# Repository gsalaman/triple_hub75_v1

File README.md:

# triple_hub75_v1
 Pi to 3 RGB chain board design

PDF:
[schematic.pdf](https://github.com/gsalaman/triple_hub75_v1/files/3968266/schematic.pdf)

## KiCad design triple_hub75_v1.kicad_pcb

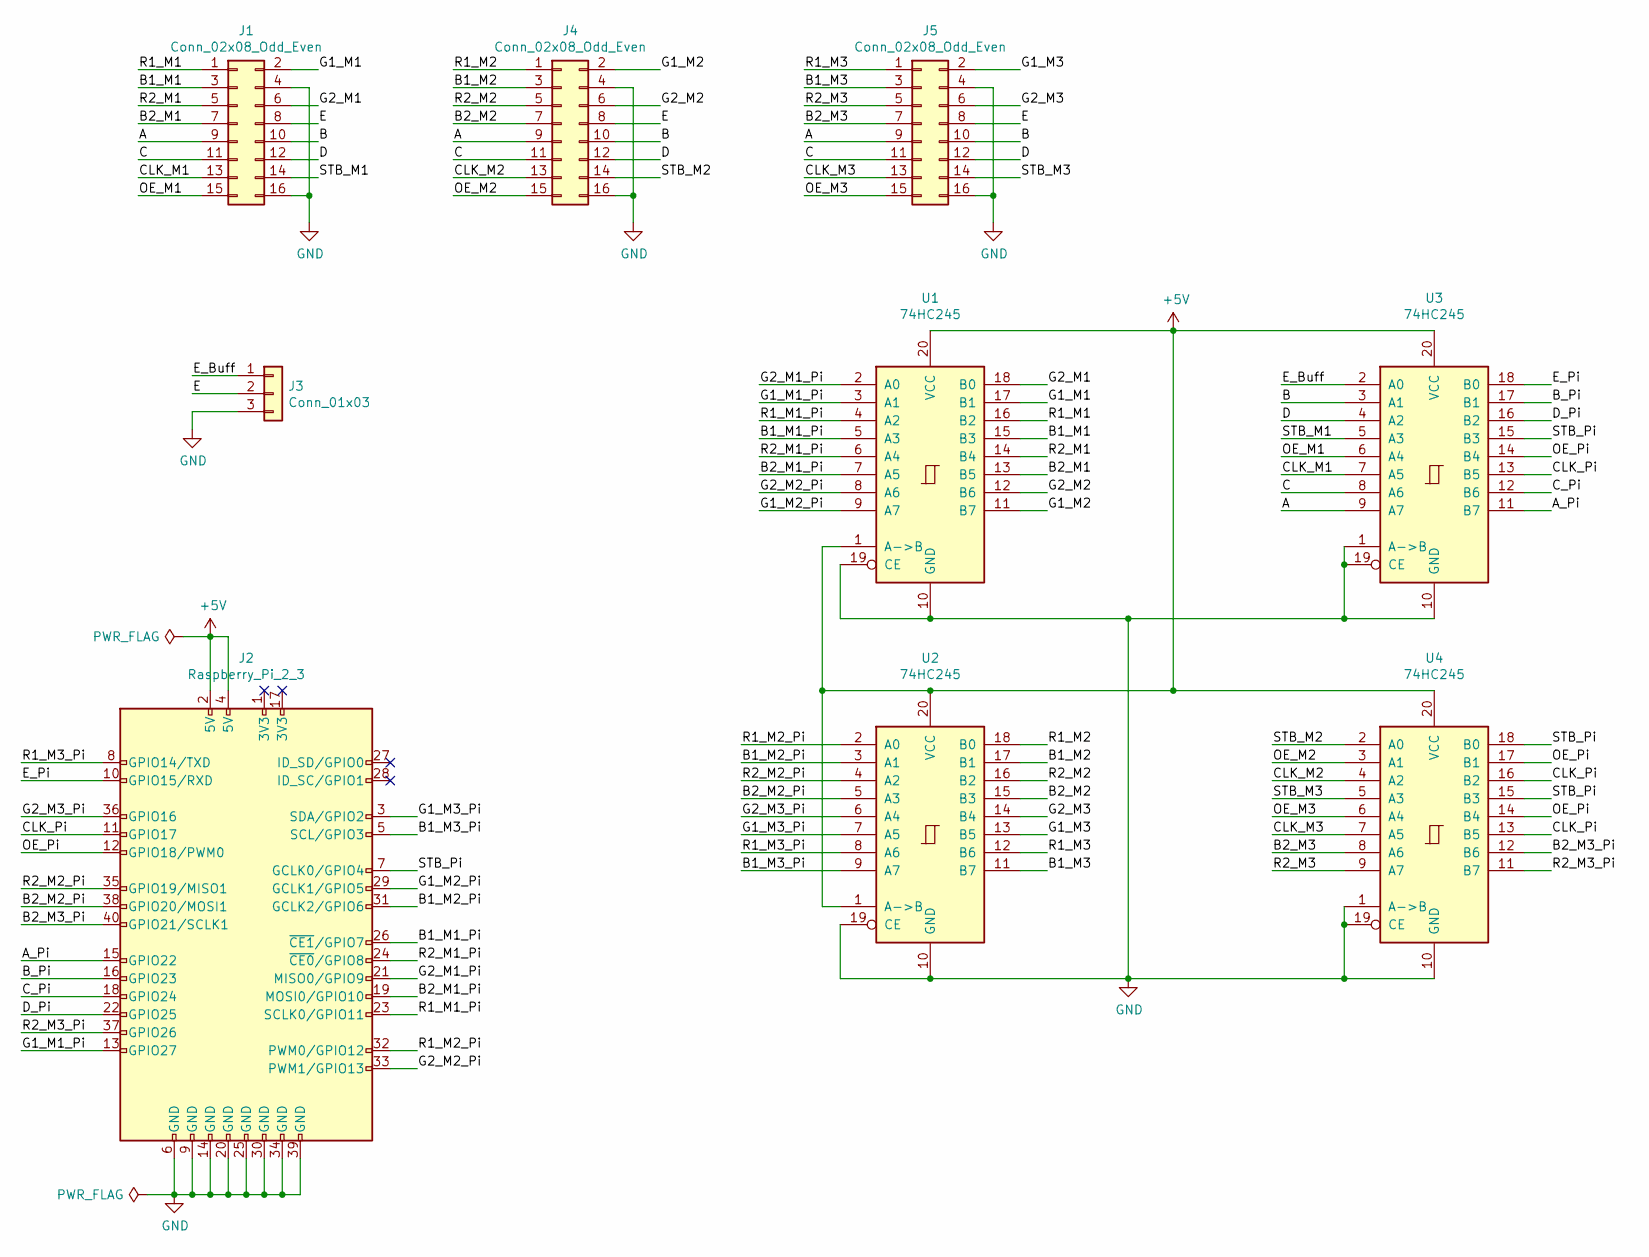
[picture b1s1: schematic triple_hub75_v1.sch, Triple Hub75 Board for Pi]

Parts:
J1, J4, J5: Conn_02x08_Odd_Even; PinHeader_2x08_P2.54mm_Vertical
J2: Raspberry_Pi_2_3; PinSocket_2x20_P2.54mm_Vertical
J3: Conn_01x03; PinHeader_1x03_P2.54mm_Vertical
U1, U2, U3, U4: 74HC245; DIP-20_W7.62mm

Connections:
+5V: J2.2 (5V), J2.4 (5V), U1.1 (A->B), U1.20 (VCC), U2.1 (A->B), U2.20 (VCC), U3.20 (VCC), U4.20 (VCC)
/A: J1.9, J4.9, J5.9, U3.9 (A7)
/A_Pi: J2.15 (GPIO22), U3.11 (B7)
/B: J1.10, J4.10, J5.10, U3.3 (A1)
/B1_M1: J1.3, U1.15 (B3)
/B1_M1_Pi: J2.26 (~CE1~/GPIO7), U1.5 (A3)
/B1_M2: J4.3, U2.17 (B1)
/B1_M2_Pi: J2.31 (GCLK2/GPIO6), U2.3 (A1)
/B1_M3: J5.3, U2.11 (B7)
/B1_M3_Pi: J2.5 (SCL/GPIO3), U2.9 (A7)
/B2_M1: J1.7, U1.13 (B5)
/B2_M1_Pi: J2.19 (MOSI0/GPIO10), U1.7 (A5)
/B2_M2: J4.7, U2.15 (B3)
/B2_M2_Pi: J2.38 (GPIO20/MOSI1), U2.5 (A3)
/B2_M3: J5.7, U4.8 (A6)
/B2_M3_Pi: J2.40 (GPIO21/SCLK1), U4.12 (B6)
/B_Pi: J2.16 (GPIO23), U3.17 (B1)
/C: J1.11, J4.11, J5.11, U3.8 (A6)
/CLK_M1: J1.13, U3.7 (A5)
/CLK_M2: J4.13, U4.4 (A2)
/CLK_M3: J5.13, U4.7 (A5)
/CLK_Pi: J2.11 (GPIO17), U3.13 (B5), U4.13 (B5), U4.16 (B2)
/C_Pi: J2.18 (GPIO24), U3.12 (B6)
/D: J1.12, J4.12, J5.12, U3.4 (A2)
/D_Pi: J2.22 (GPIO25), U3.16 (B2)
/E: J1.8, J3.2, J4.8, J5.8
/E_Buff: J3.1, U3.2 (A0)
/E_Pi: J2.10 (GPIO15/RXD), U3.18 (B0)
/G1_M1: J1.2, U1.17 (B1)
/G1_M1_Pi: J2.13 (GPIO27), U1.3 (A1)
/G1_M2: J4.2, U1.11 (B7)
/G1_M2_Pi: J2.29 (GCLK1/GPIO5), U1.9 (A7)
/G1_M3: J5.2, U2.13 (B5)
/G1_M3_Pi: J2.3 (SDA/GPIO2), U2.7 (A5)
/G2_M1: J1.6, U1.18 (B0)
/G2_M1_Pi: J2.21 (MISO0/GPIO9), U1.2 (A0)
/G2_M2: J4.6, U1.12 (B6)
/G2_M2_Pi: J2.33 (PWM1/GPIO13), U1.8 (A6)
/G2_M3: J5.6, U2.14 (B4)
/G2_M3_Pi: J2.36 (GPIO16), U2.6 (A4)
/OE_M1: J1.15, U3.6 (A4)
/OE_M2: J4.15, U4.3 (A1)
/OE_M3: J5.15, U4.6 (A4)
/OE_Pi: J2.12 (GPIO18/PWM0), U3.14 (B4), U4.14 (B4), U4.17 (B1)
/R1_M1: J1.1, U1.16 (B2)
/R1_M1_Pi: J2.23 (SCLK0/GPIO11), U1.4 (A2)
/R1_M2: J4.1, U2.18 (B0)
/R1_M2_Pi: J2.32 (PWM0/GPIO12), U2.2 (A0)
/R1_M3: J5.1, U2.12 (B6)
/R1_M3_Pi: J2.8 (GPIO14/TXD), U2.8 (A6)
/R2_M1: J1.5, U1.14 (B4)
/R2_M1_Pi: J2.24 (~CE0~/GPIO8), U1.6 (A4)
/R2_M2: J4.5, U2.16 (B2)
/R2_M2_Pi: J2.35 (GPIO19/MISO1), U2.4 (A2)
/R2_M3: J5.5, U4.9 (A7)
/R2_M3_Pi: J2.37 (GPIO26), U4.11 (B7)
/STB_M1: J1.14, U3.5 (A3)
/STB_M2: J4.14, U4.2 (A0)
/STB_M3: J5.14, U4.5 (A3)
/STB_Pi: J2.7 (GCLK0/GPIO4), U3.15 (B3), U4.15 (B3), U4.18 (B0)
GND: J1.4, J1.16, J2.6 (GND), J2.9 (GND), J2.14 (GND), J2.20 (GND), J2.25 (GND), J2.30 (GND), J2.34 (GND), J2.39 (GND), J3.3, J4.4, J4.16, J5.4, J5.16, U1.10 (GND), U1.19 (CE), U2.10 (GND), U2.19 (CE), U3.1 (A->B), U3.10 (GND), U3.19 (CE), U4.1 (A->B), U4.10 (GND), U4.19 (CE)

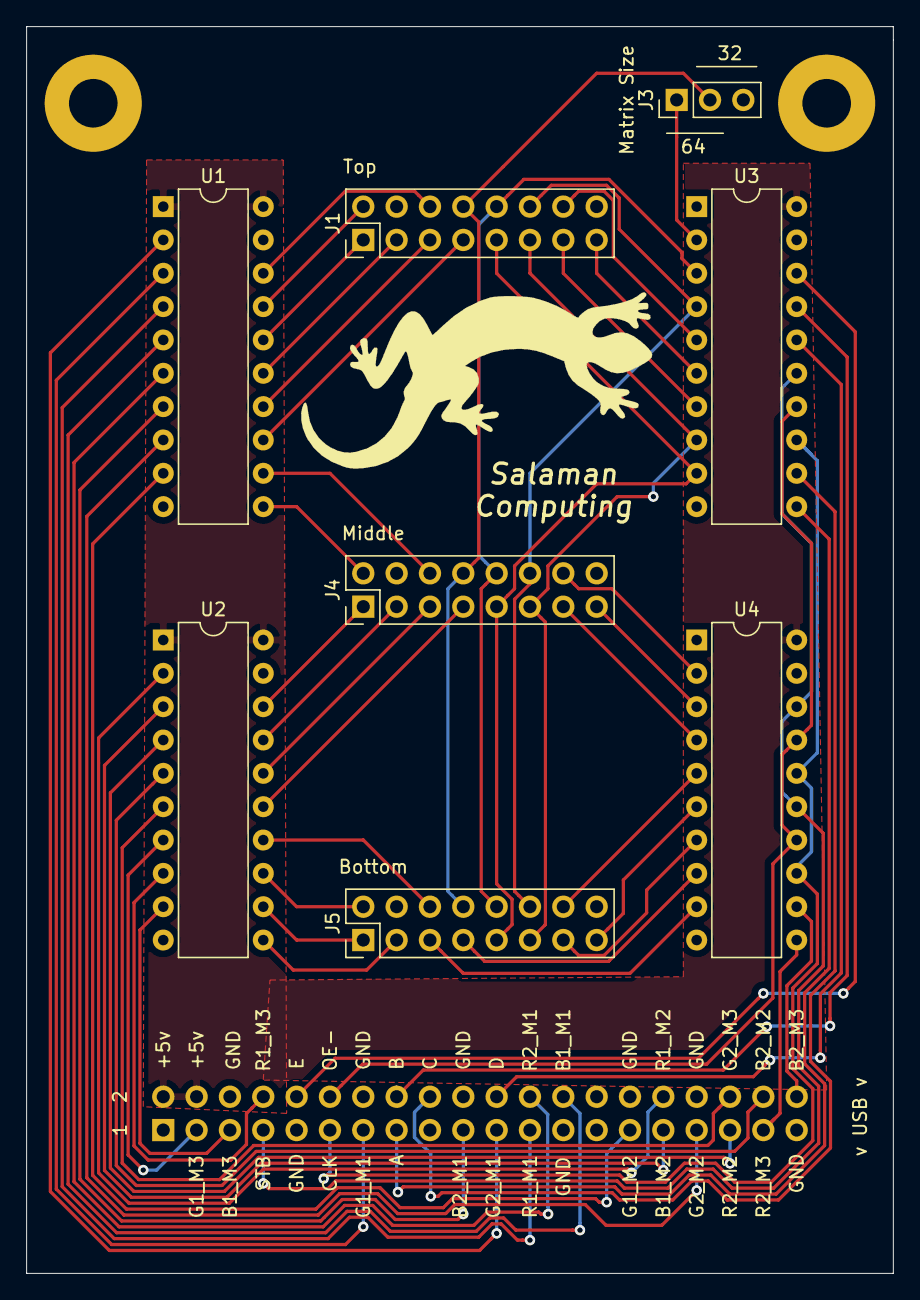
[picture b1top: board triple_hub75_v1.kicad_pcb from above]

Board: 2 copper layers, 66.0 x 95.0 mm, 9 parts (1 on the bottom side), 61 nets.

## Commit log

2019-07-27 remove left side tracks
    Step One: I want to move the left side traces from the bottom layer to the top so that I can use bottom layer as ground plane. They'll still be some on bottom, but I want to make the default the top 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
2019-07-28 U2 re-routed to top
2019-07-28 Right side routes on F-CU
    Ground fill now looks better. Next step: squeeze in the chips/traces?
2019-07-29 More squeezes
2019-07-29 ground plane finished and cleaned
2019-08-02 started silkscreen iupdates
2019-08-07 Silkscreen updates and mounting holes
2019-08-12 Final changes before V1 hits the fab
    Gerber files generated,
    Mounting holes,
    Edge cuts straightened.
